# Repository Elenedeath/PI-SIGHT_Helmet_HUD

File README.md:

# PI-SIGHT Helmet HUD

PI-SIGHT Helmet HUD는 헬멧 외부에 장착하여 사용자의 눈앞에 필요한 정보를 표시하는 헤드 업 디스플레이 장치 입니다. 사용자는 고개를 움직이지 않고도 눈앞의 디스플레이를 통해 필요한 정보 또는 후방카메라 영상을 확인할 수 있습니다.

기기의 가장 큰 특징은 소형 범용 컴퓨터인 라즈베리 파이와 교체식 모듈 시스템을 적용했다는 것입니다. 이를 통해 사용자가 직접 소프트웨어를 프로그래밍하거나 필요한 소프트웨어로 교체할 수 있고, 블루투스 헤드셋이나 GPS 모듈을 연결해 내비게이션, 레이싱 계측기, 항공 계기판 등 다양한 용도로 사용할 수 있습니다.

## 기능

 - 프리즘 디스플레이 : 눈앞에 위치한 3000cd/m^2 디스플레이를 통해 고개를 움직이거나 별도의 기기를 거치하지 않아도 필요한 정보를 확인할 수 있음
 - 범용 시스템 : 범용 리눅스 컴퓨터인 라즈베리파이를 사용해 목적에 맞는 프로그램과 센서를 쉽게 개발하여 적용할 수 있음
 - 교체형 모듈 시스템 : 프로그램과 모듈을 쉽게 교체할 수 있도록 하여 한 대의 기기를 다양한 활동에서 사용할 수 있음
 - 무선 리모컨, 후방 카메라 등 자세한 내용은 [VUDEV 웹사이트](https://sites.google.com/vudev.net/vudevnet/about-pi-sight) 또는 [설명서](https://github.com/younsj97/PI-SIGHT_Helmet_HUD/blob/main/PI-SIGHT%20%EC%82%AC%EC%9A%A9%EC%84%A4%EB%AA%85%EC%84%9C-1%20(%EB%94%94%EB%B0%94%EC%9D%B4%EC%8A%A4%20%EA%B8%B0%EB%B3%B8).pdf)를 다운로드하여 확인하세요

## 소프트웨어

 1. [Openauto](https://github.com/younsj97/PI-SIGHT_SW_Openauto) : 안드로이드 스마트폰과 연결해 안드로이드 오토 헤드 유닛으로 사용할 수 있습니다.
 2. [GPS Racer](https://github.com/younsj97/PI-SIGHT_SW_GPSRacer) : 자체 랩타이머 또는 스마트폰 연동 블루투스 GPS 수신기로 사용할 수 있습니다.
 3. [Rearview](https://github.com/younsj97/PI-SIGHT_SW_Rearview) : 실시간 후방 카메라 영상을 보여주며, 작동 중 자동으로 녹화됩니다.
 - 누구든지 필요한 프로그램과 모듈을 제작해 사용할 수 있습니다.

## 제작 방법

 - 업로드 예정

## 주의사항

 - _PI-SIGHT는 다양한 환경에서 충분한 테스트를 거치지 않았습니다. 제작과 사용은 자유지만, 그로 인해 발생하는 문제에 대하여 책임지지 않습니다._
 - _PI-SIGHT는 방진,방수를 지원하지 않습니다. 물이 들어가지 않도록 하세요_
 - _프리즘 디스플레이의 텐션 조절 볼트가 너무 느슨하면 사용 중 디스플레이가 움직여 위험할 수 있습니다_

## 커스터마이징

 - 무선 리모컨 펌웨어는 [PI-SIGHT Remote Controller SW](https://github.com/younsj97/PI-SIGHT_SW_RemoteController)를 참고하세요
 - PCB 회로 및 모듈 커넥터는 [회로](https://github.com/younsj97/PI-SIGHT_Helmet_HUD/blob/main/Documents/Circuits.pdf) 자료를 참고하세요

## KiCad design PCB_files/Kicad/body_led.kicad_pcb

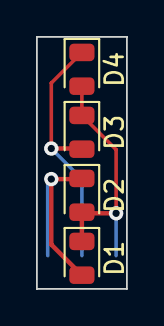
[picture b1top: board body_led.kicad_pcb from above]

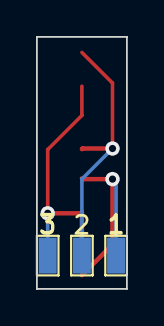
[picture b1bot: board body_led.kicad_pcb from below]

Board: 2 copper layers, 5.0 x 14.0 mm, 7 parts (3 on the bottom side), 3 nets.

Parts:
D1: 25%; LED_0805_2012Metric
D2: 50%; LED_0805_2012Metric
D3: 75%; LED_0805_2012Metric
D4: 100%; LED_0805_2012Metric
TP1: 1; TestPoint_1.0x2.0mm
TP2: 2; TestPoint_1.0x2.0mm
TP3: 3; TestPoint_1.0x2.0mm

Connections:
unnamed: D1.2 (A), D2.1 (K), TP1.1
unnamed: D1.1 (K), D2.2 (A), D3.1 (K), D4.2 (A), TP3.3
unnamed: D3.2 (A), D4.1 (K), TP2.2

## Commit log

2025-03-16 add better translated version
2025-03-16 Rename PI-SIGHT 사용설명서-1 (디바이스 기본).EN.pdf to PI-SIGHT User Manual-1 (Device Basics).EN.pdf
2025-03-18 Add Kicad Project
